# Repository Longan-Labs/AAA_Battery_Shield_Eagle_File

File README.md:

Eagle file for [AAA Battery Shield](https://www.longan-labs.cc/1040007.html)

Click on [Longan-Labs.cc](https://www.longan-labs.cc/) to get the product you need.

Contact [support@longan-labs.cc](support@longan-labs.cc) if you need help.

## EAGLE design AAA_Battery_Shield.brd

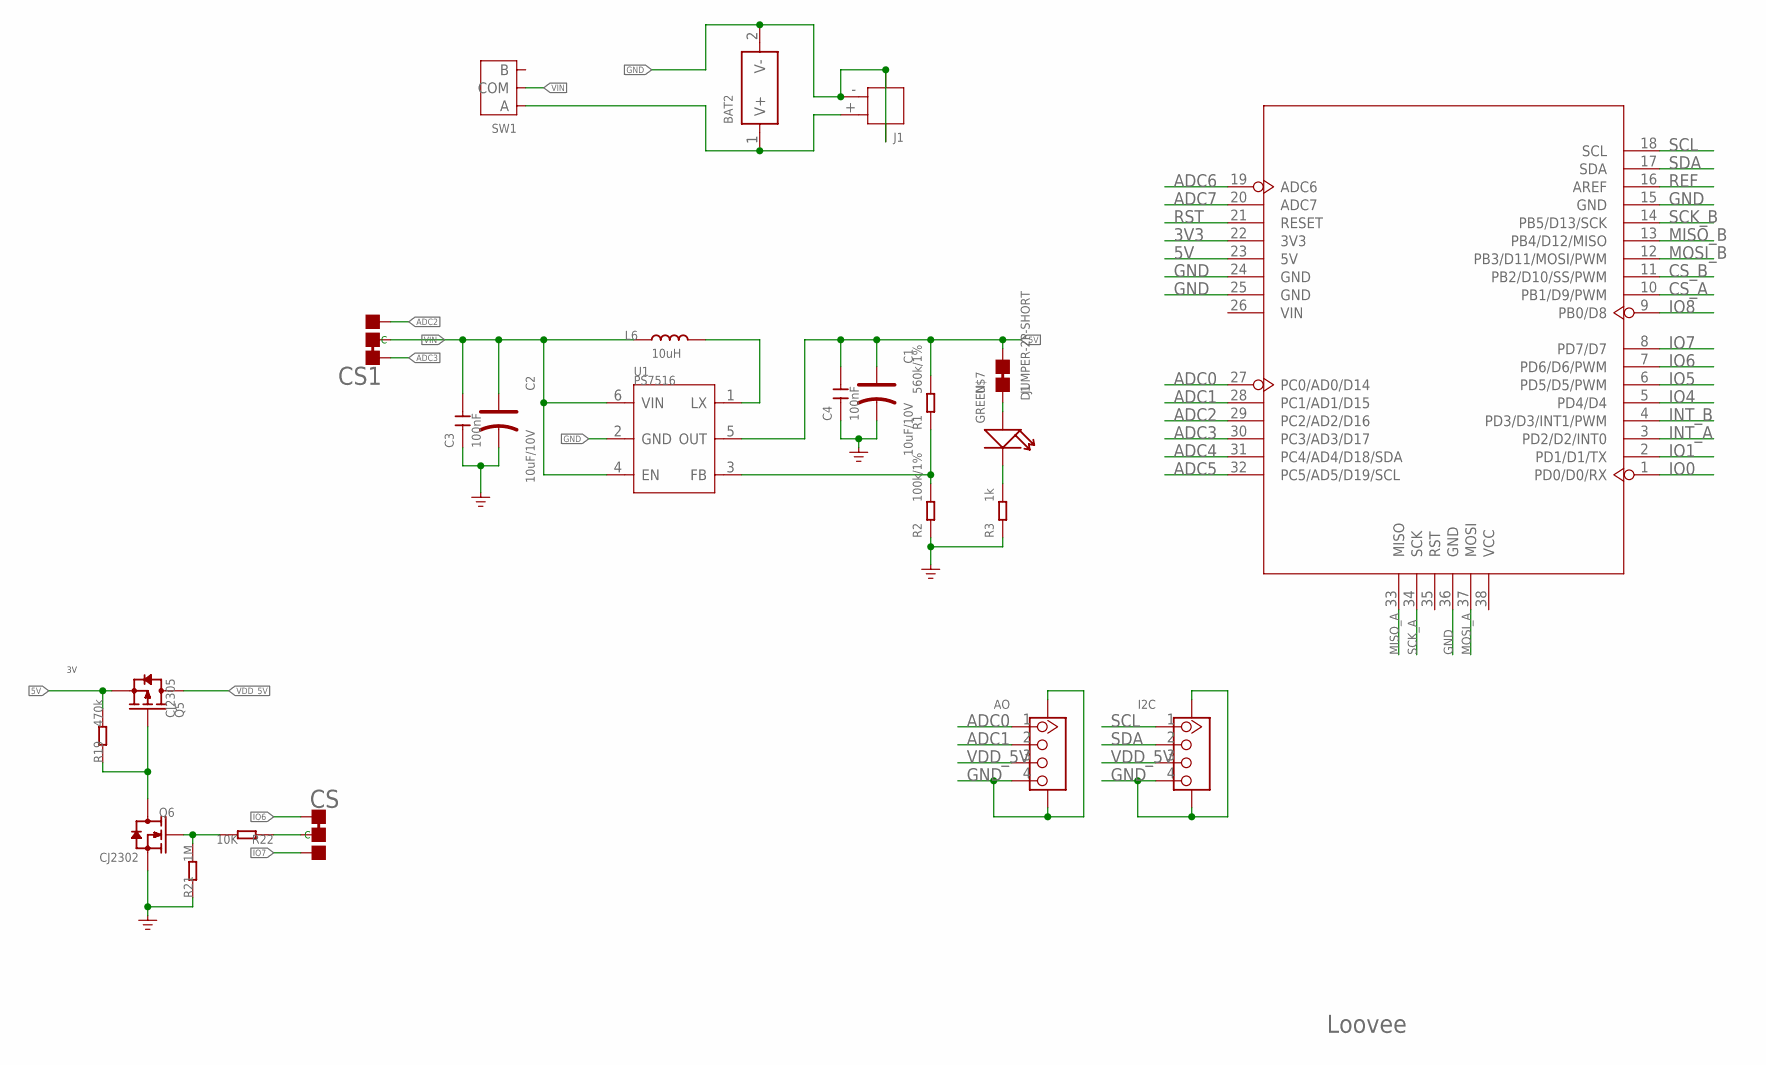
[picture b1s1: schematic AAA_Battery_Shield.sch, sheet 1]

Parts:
AO: GROVE-CONNECTOR-SMD'90D'; HW4-SMD-2.0-90D
BAT2: BAT-HOLDER-BC2AAA; BAT2P-12.5-51.8X24MM
C1, C2: 10uF/10V; AVX-B
C3, C4: 100nF; C0603
CS, CS1: JUMPER-3P-SHORT; 3P-SMD-SHORT
D1: GREEN; LED-0603
I2C: GROVE-CONNECTOR-SMD'90D'; HW4-SMD-2.0-90D
J1: JST-2P-SMD'2.0'; HW2-SMD-2.0-90D
L6: 10uH; L0420
Q5: CJ2305; SOT-23
Q6: CJ2302; SOT-23
R1: 560k/1%; R0603
R2: 100k/1%; R0603
R3: 1k; R0603
R19: 470k; R0603
R21: 1M; R0603
R22: 10K; R0603
SW1: SWITCH-2H-3P; SW3-2.5-9X3.5MM
U1: PS7516; SOT-23-6
U4: ARDUINO-38P'WITH/-SILK'; ARDUINO-38P-WITH/-SILK-500519002
U$7: JUMPER-2P-SHORT; 2P-SMD-SHORT

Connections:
3V3: U4.22 (3V3)
5V: C1.+, C4.2, Q5.2 (S), R1.2, R19.2, U1.5 (OUT), U4.23 (5V), U$7.2
ADC0: AO.1, U4.27 (PC0/AD0/D14)
ADC1: AO.2, U4.28 (PC1/AD1/D15)
ADC2: CS1.00 (R), U4.29 (PC2/AD2/D16)
ADC3: CS1.11 (L), U4.30 (PC3/AD3/D17)
ADC4: U4.31 (PC4/AD4/D18/SDA)
ADC5: U4.32 (PC5/AD5/D19/SCL)
ADC6: U4.19 (ADC6)
ADC7: U4.20 (ADC7)
CS_A: U4.10 (PB1/D9/PWM)
CS_B: U4.11 (PB2/D10/SS/PWM)
GND: AO.4, AO.SS1, AO.SS2, BAT2.2 (V-), C1.-, C2.-, C3.1, C4.1, I2C.4, I2C.SS1, I2C.SS2, J1.3, J1.4, J1.- (2), Q6.2 (S), R2.1, R3.1, R21.1, U1.2 (GND), U4.15 (GND), U4.24 (GND), U4.25 (GND), U4.36 (GND)
INT_A: U4.3 (PD2/D2/INT0)
INT_B: U4.4 (PD3/D3/INT1/PWM)
IO0: U4.1 (PD0/D0/RX)
IO1: U4.2 (PD1/D1/TX)
IO4: U4.5 (PD4/D4)
IO5: U4.6 (PD5/D5/PWM)
IO6: CS.11 (L), U4.7 (PD6/D6/PWM)
IO7: CS.00 (R), U4.8 (PD7/D7)
IO8: U4.9 (PB0/D8)
MISO_A: U4.33 (MISO)
MISO_B: U4.13 (PB4/D12/MISO)
MOSI_A: U4.37 (MOSI)
MOSI_B: U4.12 (PB3/D11/MOSI/PWM)
unnamed: BAT2.1 (V+), J1.+ (1), SW1.1 (A)
unnamed: CS.MM (C), R22.1
unnamed: D1.-, R3.2
unnamed: L6.2, U1.1 (LX)
unnamed: D1.+, U$7.1
unnamed: R1.1, R2.2, U1.3 (FB)
unnamed: Q5.1 (G), Q6.3 (D), R19.1
unnamed: Q6.1 (G), R21.2, R22.2
REF: U4.16 (AREF)
RST: U4.21 (RESET)
SCK_A: U4.34 (SCK)
SCK_B: U4.14 (PB5/D13/SCK)
SCL: I2C.1, U4.18 (SCL)
SDA: I2C.2, U4.17 (SDA)
VDD_5V: AO.3, I2C.3, Q5.3 (D)
VIN: C2.+, C3.2, CS1.MM (C), L6.1, SW1.2 (COM), U1.4 (EN), U1.6 (VIN)

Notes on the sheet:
Loovee

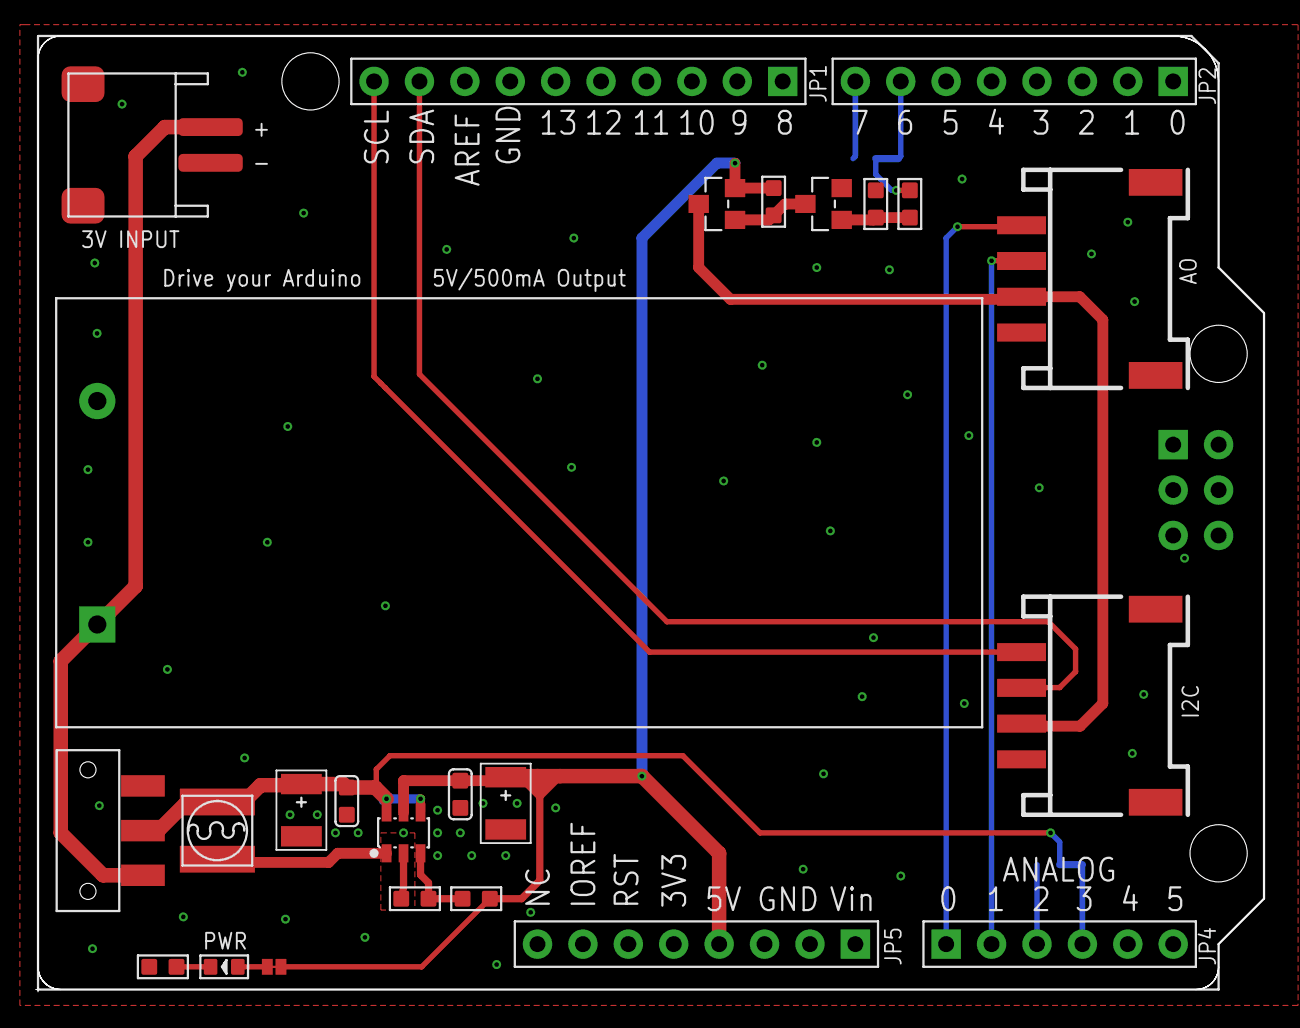
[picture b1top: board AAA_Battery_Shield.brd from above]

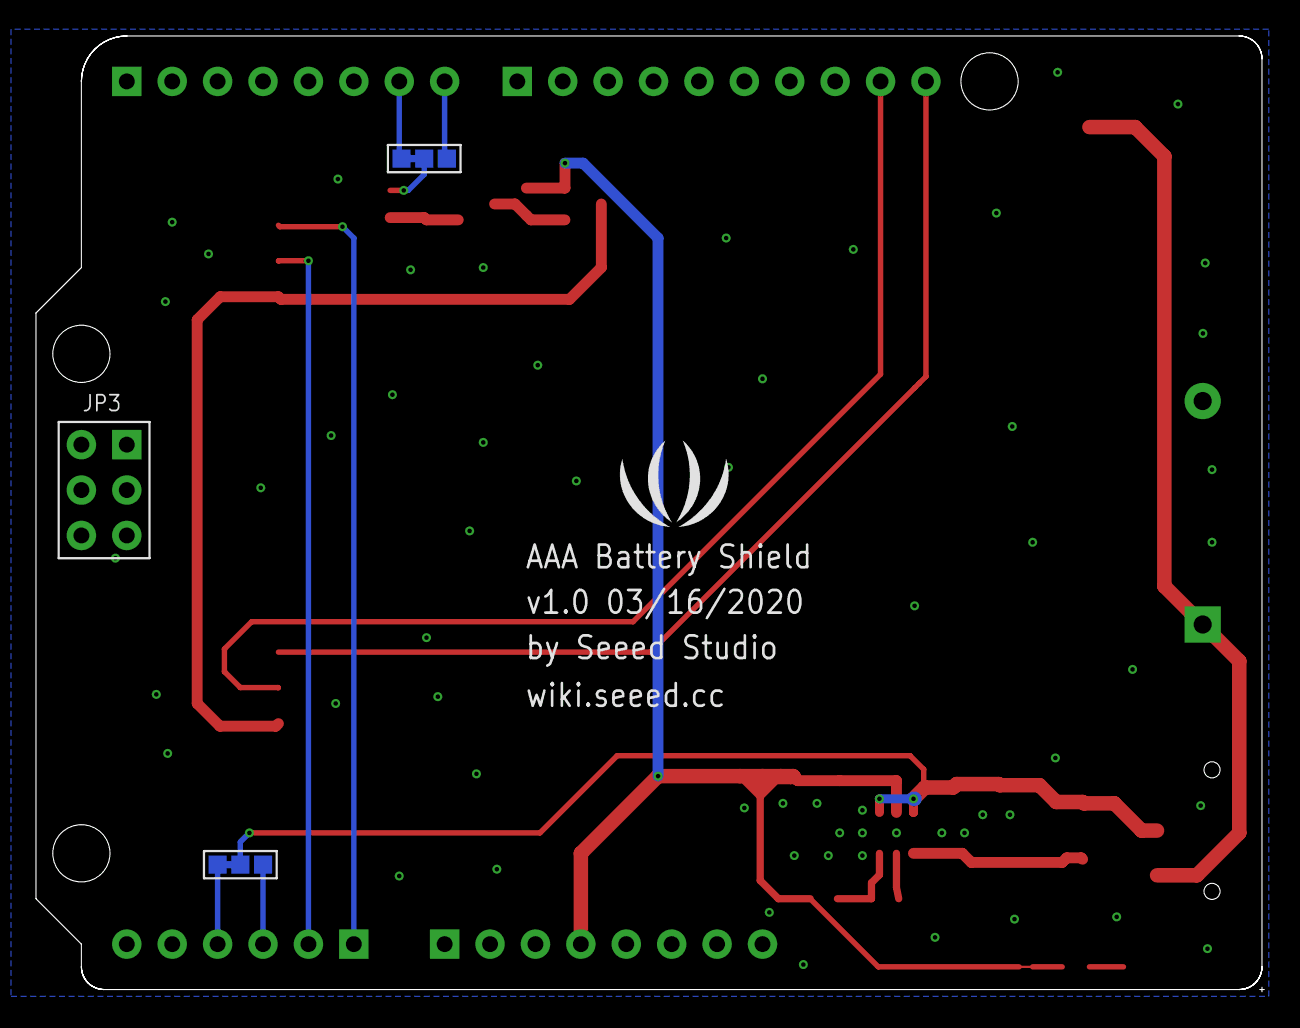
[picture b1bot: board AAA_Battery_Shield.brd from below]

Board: 2 copper layers, 68.7 x 53.5 mm, 25 parts (3 on the bottom side), 20 nets.

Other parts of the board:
U$1: LOGO_SILK

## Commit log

2020-04-14 first push
